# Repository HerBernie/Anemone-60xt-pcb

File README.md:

# Anemone 60xt pcb
  60xt keyboard with a variable layout

  🚧 **WIP**.

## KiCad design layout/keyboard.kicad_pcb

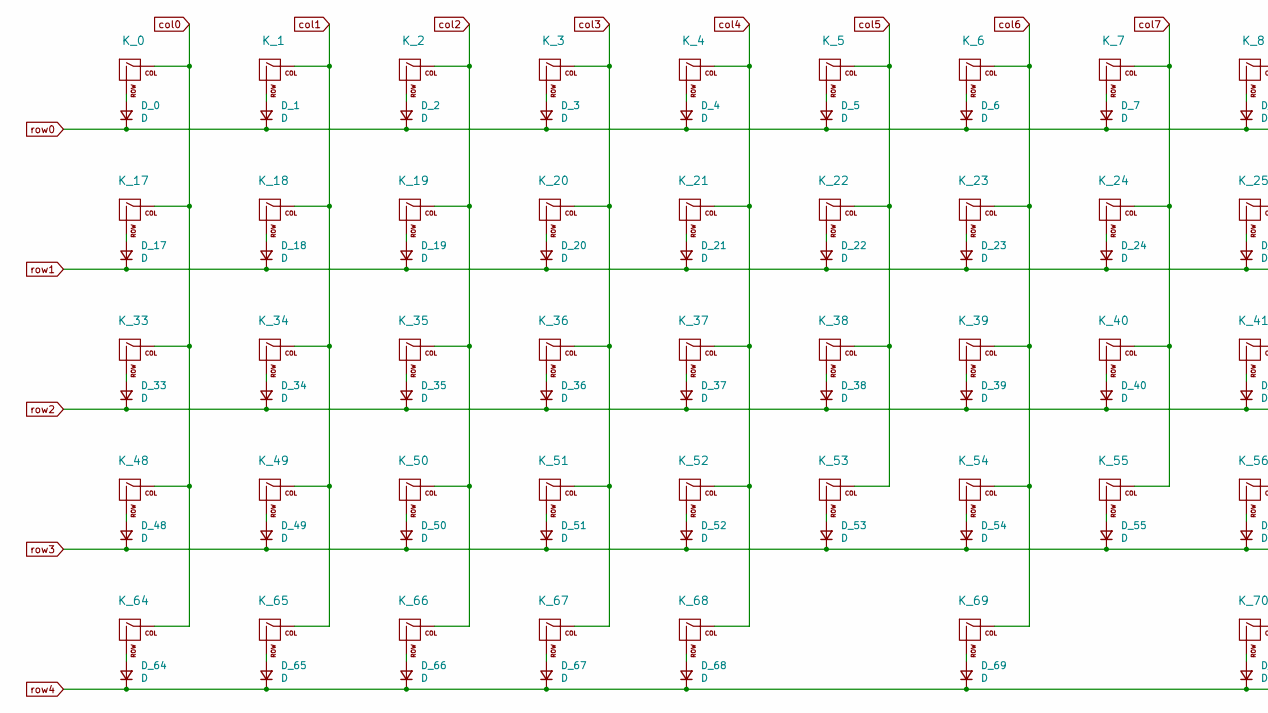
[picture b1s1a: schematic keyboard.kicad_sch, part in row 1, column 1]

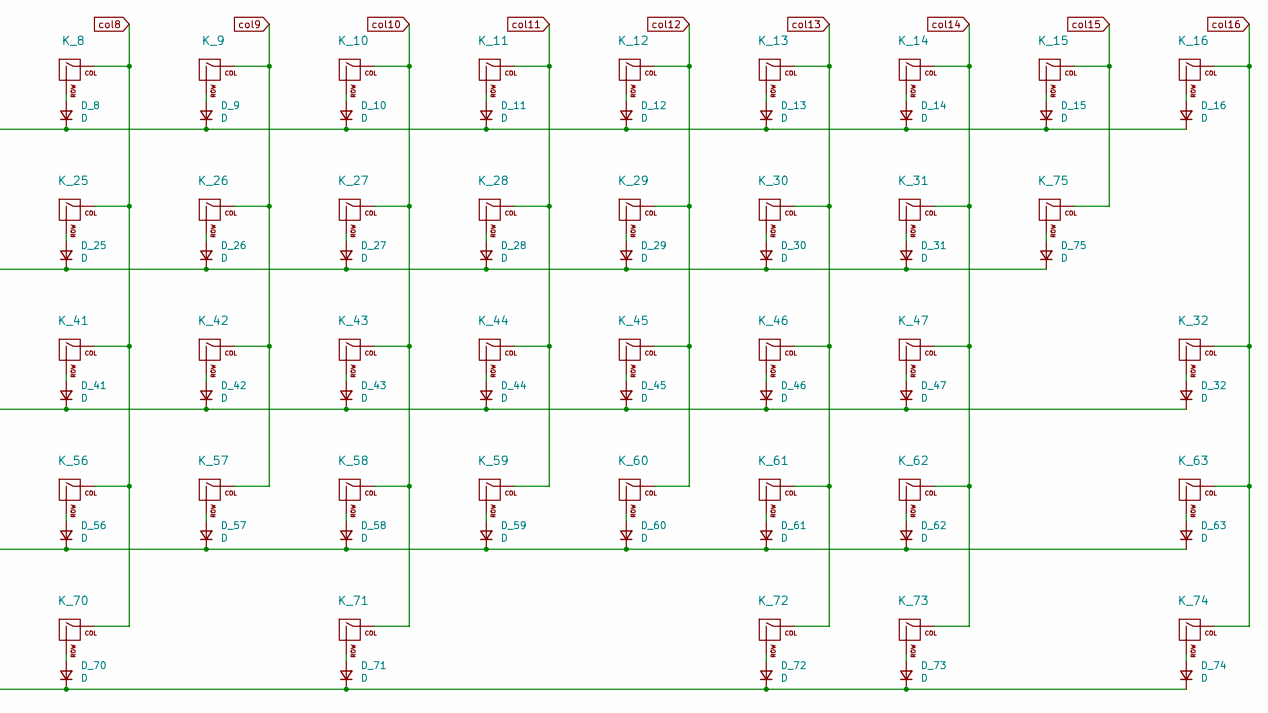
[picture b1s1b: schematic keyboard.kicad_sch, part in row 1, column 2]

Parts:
D_0, D_1, D_2, D_3, D_4, D_5, D_6, D_7, D_8, D_9, D_10, D_11, D_12, D_13, D_14, D_15, D_16, D_17, D_18, D_19, D_20, D_21, D_22, D_23, D_24, D_25, D_26, D_27, D_28, D_29, D_30, D_31, D_32, D_33, D_34, D_35, D_36, D_37, D_38, D_39, D_40, D_41, D_42, D_43, D_44, D_45, D_46, D_47, D_48, D_49, D_50, D_51, D_52, D_53, D_54, D_55, D_56, D_57, D_58, D_59, D_60, D_61, D_62, D_63, D_64, D_65, D_66, D_67, D_68, D_69, D_70, D_71, D_72, D_73, D_74, D_75: D; D_SOD-123
K_0, K_1, K_2, K_3, K_4, K_5, K_6, K_7, K_8, K_9, K_10, K_11, K_12, K_13, K_14, K_15, K_16, K_17, K_18, K_20, K_21, K_22, K_23, K_24, K_25, K_26, K_27, K_28, K_29, K_30, K_31, K_33, K_34, K_36, K_37, K_38, K_39, K_40, K_41, K_42, K_43, K_44, K_45, K_46, K_47, K_48, K_49, K_51, K_52, K_53, K_54, K_55, K_56, K_57, K_58, K_59, K_60, K_61, K_63, K_64, K_65, K_67, K_70, K_73, K_75: KEYSW; MX-1U-NoLED
K_19, K_66, K_68, K_72, K_74: KEYSW; MX-1.5U-NoLED
K_32, K_35, K_50: KEYSW; MX-1.25U-NoLED
K_62: KEYSW; MX-1.75U-NoLED
K_69, K_71: KEYSW; MX-3U-NoLED

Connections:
unnamed: D_0.2 (A), K_0.2 (ROW)
unnamed: D_1.2 (A), K_1.2 (ROW)
unnamed: D_2.2 (A), K_2.2 (ROW)
unnamed: D_3.2 (A), K_3.2 (ROW)
unnamed: D_4.2 (A), K_4.2 (ROW)
unnamed: D_5.2 (A), K_5.2 (ROW)
unnamed: D_6.2 (A), K_6.2 (ROW)
unnamed: D_7.2 (A), K_7.2 (ROW)
unnamed: D_8.2 (A), K_8.2 (ROW)
unnamed: D_9.2 (A), K_9.2 (ROW)
unnamed: D_10.2 (A), K_10.2 (ROW)
unnamed: D_11.2 (A), K_11.2 (ROW)
unnamed: D_12.2 (A), K_12.2 (ROW)
unnamed: D_13.2 (A), K_13.2 (ROW)
unnamed: D_14.2 (A), K_14.2 (ROW)
unnamed: D_15.2 (A), K_15.2 (ROW)
unnamed: D_16.2 (A), K_16.2 (ROW)
unnamed: D_17.2 (A), K_17.2 (ROW)
unnamed: D_18.2 (A), K_18.2 (ROW)
unnamed: D_19.2 (A), K_19.2 (ROW)
unnamed: D_20.2 (A), K_20.2 (ROW)
unnamed: D_21.2 (A), K_21.2 (ROW)
unnamed: D_22.2 (A), K_22.2 (ROW)
unnamed: D_23.2 (A), K_23.2 (ROW)
unnamed: D_24.2 (A), K_24.2 (ROW)
unnamed: D_25.2 (A), K_25.2 (ROW)
unnamed: D_26.2 (A), K_26.2 (ROW)
unnamed: D_27.2 (A), K_27.2 (ROW)
unnamed: D_28.2 (A), K_28.2 (ROW)
unnamed: D_29.2 (A), K_29.2 (ROW)
unnamed: D_30.2 (A), K_30.2 (ROW)
unnamed: D_31.2 (A), K_31.2 (ROW)
unnamed: D_32.2 (A), K_32.2 (ROW)
unnamed: D_33.2 (A), K_33.2 (ROW)
unnamed: D_34.2 (A), K_34.2 (ROW)
unnamed: D_35.2 (A), K_35.2 (ROW)
unnamed: D_36.2 (A), K_36.2 (ROW)
unnamed: D_37.2 (A), K_37.2 (ROW)
unnamed: D_38.2 (A), K_38.2 (ROW)
unnamed: D_39.2 (A), K_39.2 (ROW)
unnamed: D_40.2 (A), K_40.2 (ROW)
unnamed: D_41.2 (A), K_41.2 (ROW)
unnamed: D_42.2 (A), K_42.2 (ROW)
unnamed: D_43.2 (A), K_43.2 (ROW)
unnamed: D_44.2 (A), K_44.2 (ROW)
unnamed: D_45.2 (A), K_45.2 (ROW)
unnamed: D_46.2 (A), K_46.2 (ROW)
unnamed: D_47.2 (A), K_47.2 (ROW)
unnamed: D_48.2 (A), K_48.2 (ROW)
unnamed: D_49.2 (A), K_49.2 (ROW)
unnamed: D_50.2 (A), K_50.2 (ROW)
unnamed: D_51.2 (A), K_51.2 (ROW)
unnamed: D_52.2 (A), K_52.2 (ROW)
unnamed: D_53.2 (A), K_53.2 (ROW)
unnamed: D_54.2 (A), K_54.2 (ROW)
unnamed: D_55.2 (A), K_55.2 (ROW)
unnamed: D_56.2 (A), K_56.2 (ROW)
unnamed: D_57.2 (A), K_57.2 (ROW)
unnamed: D_58.2 (A), K_58.2 (ROW)
unnamed: D_59.2 (A), K_59.2 (ROW)
unnamed: D_60.2 (A), K_60.2 (ROW)
unnamed: D_61.2 (A), K_61.2 (ROW)
unnamed: D_62.2 (A), K_62.2 (ROW)
unnamed: D_63.2 (A), K_63.2 (ROW)
unnamed: D_64.2 (A), K_64.2 (ROW)
unnamed: D_65.2 (A), K_65.2 (ROW)
unnamed: D_66.2 (A), K_66.2 (ROW)
unnamed: D_67.2 (A), K_67.2 (ROW)
unnamed: D_68.2 (A), K_68.2 (ROW)
unnamed: D_69.2 (A), K_69.2 (ROW)
unnamed: D_70.2 (A), K_70.2 (ROW)
unnamed: D_71.2 (A), K_71.2 (ROW)
unnamed: D_72.2 (A), K_72.2 (ROW)
unnamed: D_73.2 (A), K_73.2 (ROW)
unnamed: D_74.2 (A), K_74.2 (ROW)
unnamed: D_75.2 (A), K_75.2 (ROW)
col0: K_0.1 (COL), K_17.1 (COL), K_33.1 (COL), K_48.1 (COL), K_64.1 (COL)
col1: K_1.1 (COL), K_18.1 (COL), K_34.1 (COL), K_49.1 (COL), K_65.1 (COL)
col2: K_2.1 (COL), K_19.1 (COL), K_35.1 (COL), K_50.1 (COL), K_66.1 (COL)
col3: K_3.1 (COL), K_20.1 (COL), K_36.1 (COL), K_51.1 (COL), K_67.1 (COL)
col4: K_4.1 (COL), K_21.1 (COL), K_37.1 (COL), K_52.1 (COL), K_68.1 (COL)
col5: K_5.1 (COL), K_22.1 (COL), K_38.1 (COL), K_53.1 (COL)
col6: K_6.1 (COL), K_23.1 (COL), K_39.1 (COL), K_54.1 (COL), K_69.1 (COL)
col7: K_7.1 (COL), K_24.1 (COL), K_40.1 (COL), K_55.1 (COL)
col8: K_8.1 (COL), K_25.1 (COL), K_41.1 (COL), K_56.1 (COL), K_70.1 (COL)
col9: K_9.1 (COL), K_26.1 (COL), K_42.1 (COL), K_57.1 (COL)
col10: K_10.1 (COL), K_27.1 (COL), K_43.1 (COL), K_58.1 (COL), K_71.1 (COL)
col11: K_11.1 (COL), K_28.1 (COL), K_44.1 (COL), K_59.1 (COL)
col12: K_12.1 (COL), K_29.1 (COL), K_45.1 (COL), K_60.1 (COL)
col13: K_13.1 (COL), K_30.1 (COL), K_46.1 (COL), K_61.1 (COL), K_72.1 (COL)
col14: K_14.1 (COL), K_31.1 (COL), K_47.1 (COL), K_62.1 (COL), K_73.1 (COL)
col15: K_15.1 (COL), K_75.1 (COL)
col16: K_16.1 (COL), K_32.1 (COL), K_63.1 (COL), K_74.1 (COL)
row0: D_0.1 (K), D_1.1 (K), D_2.1 (K), D_3.1 (K), D_4.1 (K), D_5.1 (K), D_6.1 (K), D_7.1 (K), D_8.1 (K), D_9.1 (K), D_10.1 (K), D_11.1 (K), D_12.1 (K), D_13.1 (K), D_14.1 (K), D_15.1 (K), D_16.1 (K)
row1: D_17.1 (K), D_18.1 (K), D_19.1 (K), D_20.1 (K), D_21.1 (K), D_22.1 (K), D_23.1 (K), D_24.1 (K), D_25.1 (K), D_26.1 (K), D_27.1 (K), D_28.1 (K), D_29.1 (K), D_30.1 (K), D_31.1 (K), D_75.1 (K)
row2: D_32.1 (K), D_33.1 (K), D_34.1 (K), D_35.1 (K), D_36.1 (K), D_37.1 (K), D_38.1 (K), D_39.1 (K), D_40.1 (K), D_41.1 (K), D_42.1 (K), D_43.1 (K), D_44.1 (K), D_45.1 (K), D_46.1 (K), D_47.1 (K)
row3: D_48.1 (K), D_49.1 (K), D_50.1 (K), D_51.1 (K), D_52.1 (K), D_53.1 (K), D_54.1 (K), D_55.1 (K), D_56.1 (K), D_57.1 (K), D_58.1 (K), D_59.1 (K), D_60.1 (K), D_61.1 (K), D_62.1 (K), D_63.1 (K)
row4: D_64.1 (K), D_65.1 (K), D_66.1 (K), D_67.1 (K), D_68.1 (K), D_69.1 (K), D_70.1 (K), D_71.1 (K), D_72.1 (K), D_73.1 (K), D_74.1 (K)

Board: 2 copper layers, 150 parts (75 on the bottom side), 96 nets, no tracks yet.

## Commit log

2023-06-25 Add submodules, libraries
2023-06-26 organize projects
2023-06-26 Create MCU schematic
2023-06-26 Initialize the matrix
2023-06-27 Create LICENSE
